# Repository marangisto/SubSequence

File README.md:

# SubSequence
Modular Sequencer Sub-Module

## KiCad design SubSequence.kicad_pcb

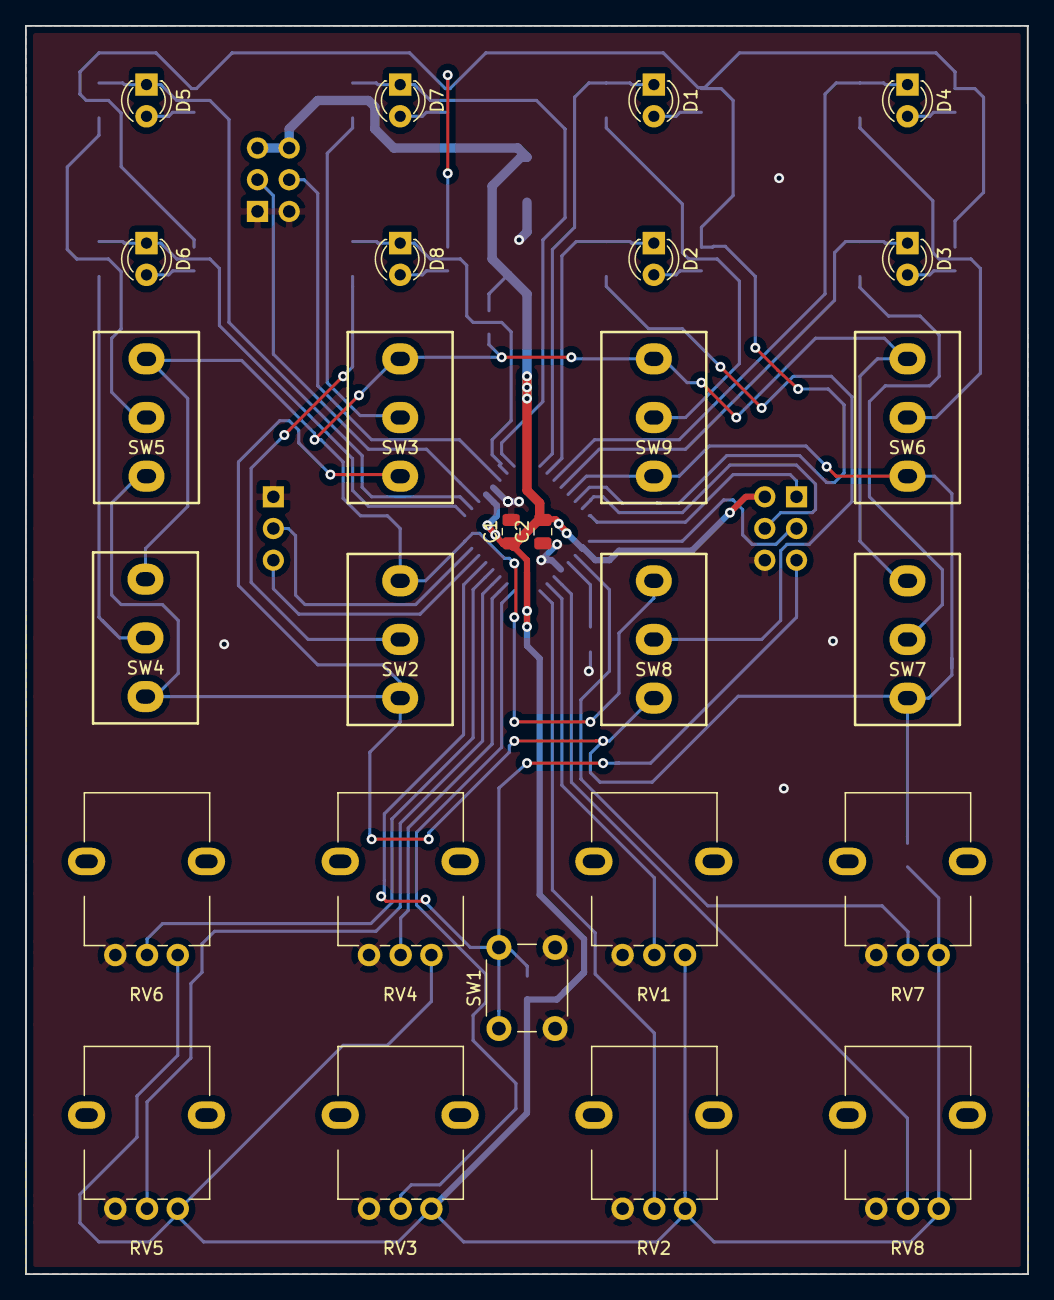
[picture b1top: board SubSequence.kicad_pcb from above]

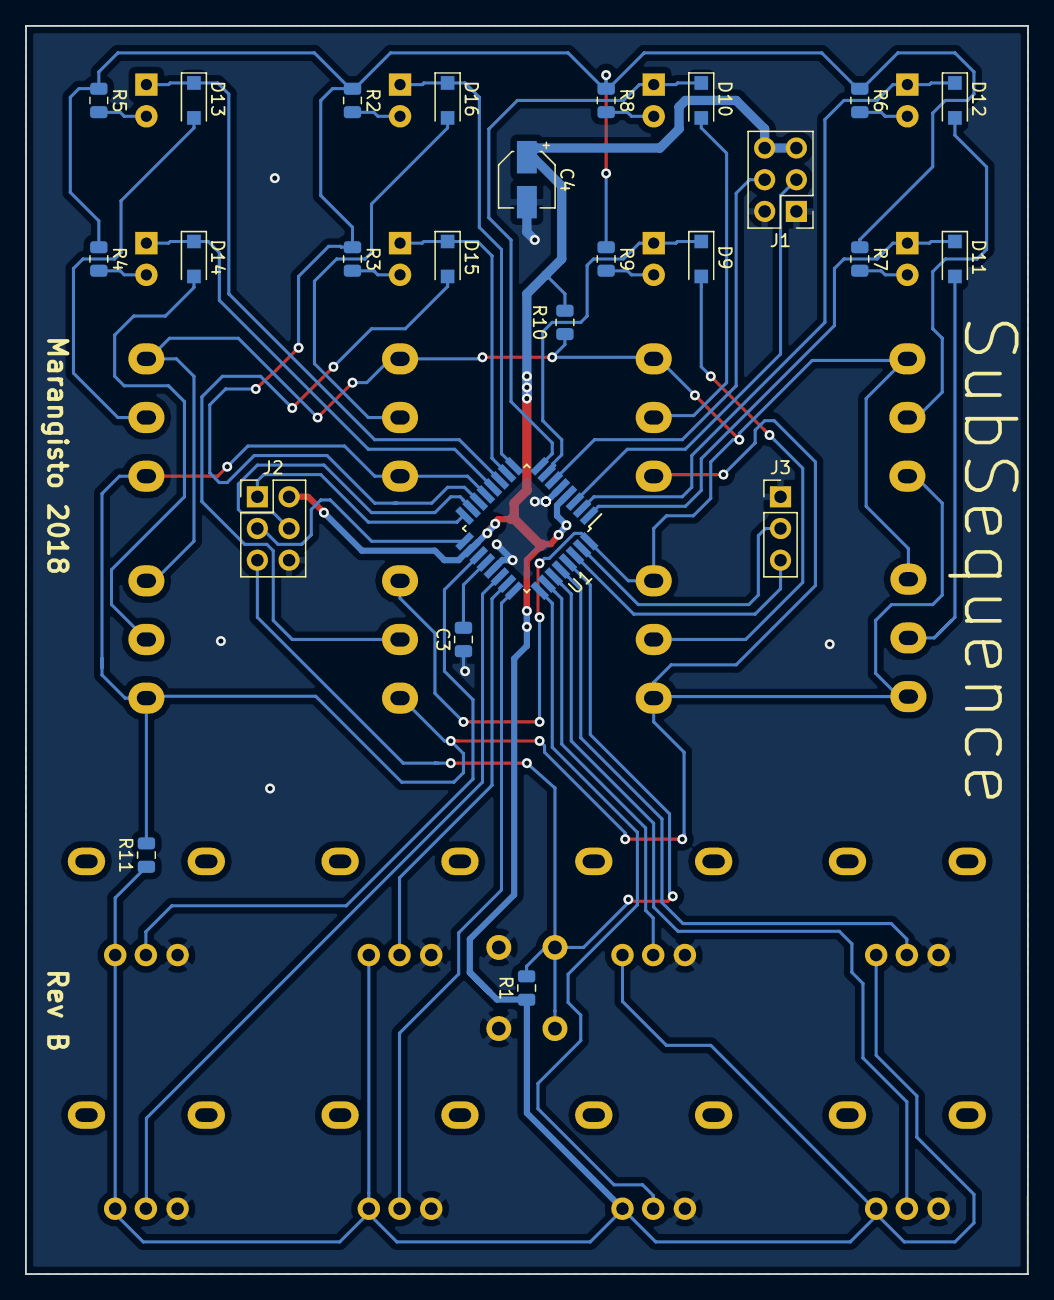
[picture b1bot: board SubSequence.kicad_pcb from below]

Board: 2 copper layers, 80.3 x 100.0 mm, 52 parts (25 on the bottom side), 46 nets.

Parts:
C1, C2, C3: 100n; C_0805_2012Metric
C4: 10u; CP_Elec_4x5.8
D1, D2, D3, D4, D5, D6, D7, D8: LED; LED_D3.0mm
D9, D10, D11, D12, D13, D14, D15, D16: 1N4148; D_SOD-123F
J1, J2: Conn_02x03_Odd_Even; PinHeader_2x03_P2.54mm_Vertical
J3: Conn_01x03; PinHeader_1x03_P2.54mm_Vertical
R1, R10, R11: 10k; R_0805_2012Metric
R2, R3, R4, R5, R6, R7, R8, R9: 330; R_0805_2012Metric
RV1, RV2, RV3, RV4, RV5, RV6, RV7, RV8: 100k; AlpsRK09K
SW1: SW_Push; SW_PUSH_6mm_H9.5mm
SW2, SW3, SW4, SW5, SW6, SW7, SW8, SW9: SW_SPDT_MSM; SPDT
U1: ATmega328PB-AU; TQFP-32_7x7mm_P0.8mm

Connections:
+5V: C1.1, C2.2, C4.1, J1.5, J1.6, J2.2, R1.1, R10.1, R11.1, RV1.1, RV2.1, RV3.1, RV4.1, RV5.1, RV6.1, RV7.1, RV8.1, U1.4, U1.18
/MCU328/PB0: D3.1, D14.1, U1.12
/MCU328/PB1: R11.2, SW2.1, SW3.1, SW4.1, SW5.1, SW6.1, SW7.1, SW8.1, SW9.1, U1.13
/MCU328/PB2: R2.1, R3.1, R4.1, R5.1, R6.1, R7.1, R8.1, R9.1, U1.14
/MCU328/PB6: D8.1, D9.1, U1.7
/MCU328/PB7: D7.1, D10.1, U1.8
/MCU328/PC0: RV1.2, U1.23
/MCU328/PC1: RV2.2, U1.24
/MCU328/PC2: RV3.2, U1.25
/MCU328/PC3: RV4.2, U1.26
/MCU328/PC4: RV5.2, U1.27
/MCU328/PC5: RV6.2, U1.28
/MCU328/PD2: R10.2, SW2.3, SW3.3, SW4.3, SW5.3, SW6.3, SW7.3, SW8.3, SW9.3, U1.32
/MCU328/PD3: D6.1, D11.1, U1.1
/MCU328/PD4: D5.1, D12.1, U1.2
/MCU328/PD5: D1.1, D16.1, U1.9
/MCU328/PD6: D2.1, D15.1, U1.10
/MCU328/PD7: D4.1, D13.1, U1.11
/MCU328/PE2: RV7.2, U1.19
/MCU328/PE3: RV8.2, U1.22
/MCU328/RXD/PD0: J3.3, U1.30
/MCU328/TXD/PD1: J3.2, U1.31
GND: C1.2, C2.1, C3.1, C4.2, J1.1, J1.2, J2.6, J3.1, RV1.3, RV2.3, RV3.3, RV4.3, RV5.3, RV6.3, RV7.3, RV8.3, SW1.2, U1.5, U1.21
unnamed: C3.2, U1.20
unnamed: D1.2, R2.2
unnamed: D2.2, R3.2
unnamed: D3.2, R4.2
unnamed: D4.2, R5.2
unnamed: D5.2, R6.2
unnamed: D6.2, R7.2
unnamed: D7.2, R8.2
unnamed: D8.2, R9.2
unnamed: D9.2, SW2.2
unnamed: D10.2, SW3.2
unnamed: D11.2, SW4.2
unnamed: D12.2, SW5.2
unnamed: D13.2, SW6.2
unnamed: D14.2, SW7.2
unnamed: D15.2, SW8.2
unnamed: D16.2, SW9.2
unnamed: J2.1, U1.16
unnamed: J2.3, U1.17
unnamed: J2.4, U1.15
unnamed: J2.5, R1.2, SW1.1, U1.29
SCL: J1.4, U1.6
SDA: J1.3, U1.3

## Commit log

2018-09-27 Added inital design.
2018-09-28 Finished layout.
2018-09-29 Silk-screens.
2018-10-02 Added BOM.
2018-10-02 Added Gerbers.
2018-10-06 Save Gerber settings.
2018-11-04 Added pull-up resistors.
2018-11-07 Added 3-d models (except toggle switches).
2018-11-08 Added 3d-model for toggle switch.
2018-11-08 Added rendering of front.
2018-11-08 Added drafting image of toggle switch.
2018-11-08 Corrected arm material on 3d-model.
2018-11-08 Added Fusion 360 rendering of SPDT.
2018-11-10 Added PCB mount footprint for SPDT.
2018-11-10 Initial revision B of board, now using PCB mounted SPDT.
2019-01-02 Renamed rendering.
2019-01-02 Added more renderings.
2019-01-02 Upgraded to KiCad 5.02.
2019-05-05 Added firmware (moved from AVR project).
